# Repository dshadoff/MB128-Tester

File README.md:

# MB128-Tester
This project contains both a PC board to control (Backup, Restore, Test) PC Engine
Memory Base 128 devices, as well as the control software for that PC board.

The original PC board is based on an 'Adafruit Feather M0 Adalogger' microcontroller board, which
directly interfaces to PC Engine Memory Base 128 devices.

There is also an updated version which is based on the Seeed Studios Wio Terminal device, which is
more of a finished all-in-one unit with a screen.

This repository holds the software which runs on those devices, as well as the boards' design files.

The sketch was built within the Arduino IDE, but I found that the digitalWrite() and digitalRead()
functions were too slow: ~1uS per call, when I needed 3 to 4 times that speed.

Moreover, they could only manipulate one pin at a time, when I generally needed to write 2, or read 4.

As a result, you will see direct port reads/writes to the Cortex M0 (or M4) ports... see the comments at the
top of the sketch if this is confusing.

(Note: Older versions of this sketch were written for an older version of the board, which didn't have
status LEDs or pushbutton switches, and automatically started to read the MB128 at boot-up time.)

Instructions on use:
--------------------

To use any of the functionality, ensure that the MB128 is plugged into the port, and an SDCard is
inserted into the SDCard slot of the Microcontroller board.  Finally, then attach the USB cable
in order to apply power ot the board.

- M0 Adalogger board:
A short self-test will take place, and all of the LEDs will flash briefly.  Once this has completed
and the Feather's green LED is on, you may press a button.

- Wio Terminal:
A short self-test will take place, with status updates appearing on screen.  Once this has completed,
the screen will display a choice of operations (associated with the buttons across the top edge).

Backup:
-------
The device will backup the contents of the MB128 onto the SDCard, creating a file in the root
directory, with the filename: 'MB128_xx.SAV' (where 'xx' is a 2-digit number).  Multiple versions
of backups will be added to the SDCard until 99 versions have been reached.
A backup takes slightly over 10 seconds.

Restore:
--------
The device will use the highest-numbered 'MB128_xx.SAV' file in the root directory of the card,
and load the contents into the MB128.
A restore takes slightly over 10 seconds.

Test:
-----
The device will first create a temporary backup of the contents of the device, then will write,
read, and verify test patterns to all location on the MB128, finally restoring the original
contents.  The backup is saved into a file named 'TESTTEMP.BKP' in the root directory of the
SDCard.
A test takes slightly over one minute.

Error conditions:
-----------------
- If the 'SDCard Error' LED lights up at startup, there is a problem with the SDCard
- If the 'MB128 Error' LED lights up at startup, there is a problem with the MB128
(On the Wio Terminal version, clear error messages will appear on the screen).

- If either of the above LEDs go into a flashing state, this is an error which happened during
the process of reading or writing.  Please reset the device and/or turn the power off and back on

- In order to reset the device, there is a small pushbutton on the  microcontroller board. Do
not push this under normal circumstances, but you can press it if there is a flashing LED on
the MB128 reader.  If pressed, the MB128 may be interrupted in the middle of a protocol, causing
errors immedaitely afterward.  If this happens, unplug the MB128 from the reader, wait several
seconds, and plug it back in.  Then reset the microcontroller once again.

Additional information:
-----------------------
- If the USB is connected to a PC, and a terminal program is opened (19200 baud) for the
pseudo-serial port, messages indicating progress or errors will be displayed.

Original Board (Adalogger M0)
-----------------------------

Wio Terminal (Rev. A, in use)
-----------------------------

Daughterboard
-------------

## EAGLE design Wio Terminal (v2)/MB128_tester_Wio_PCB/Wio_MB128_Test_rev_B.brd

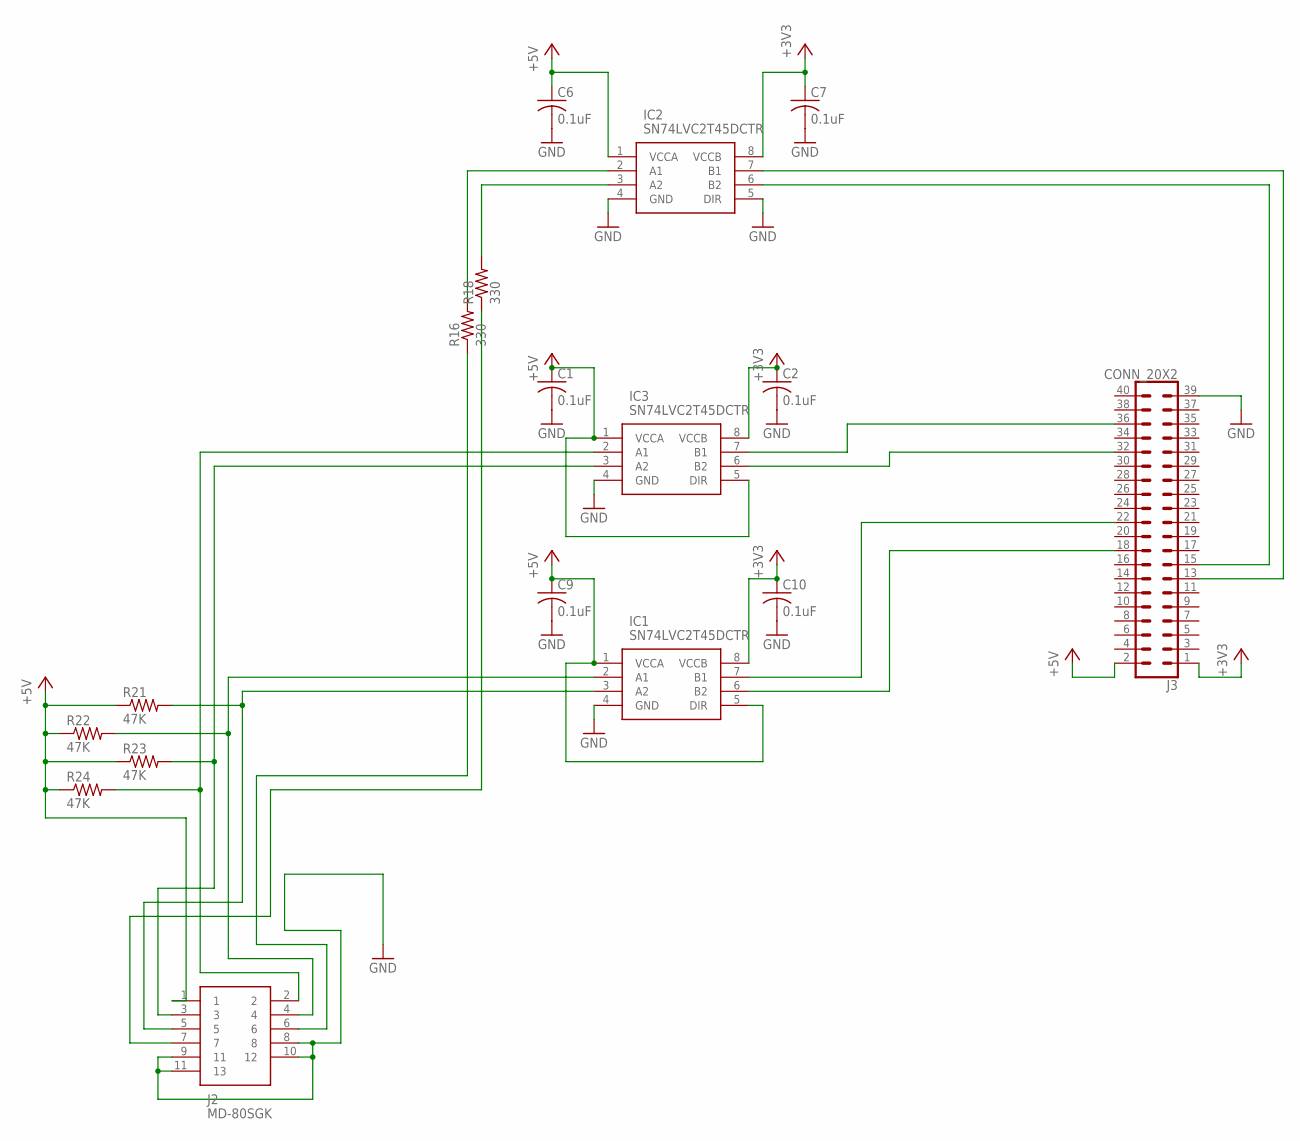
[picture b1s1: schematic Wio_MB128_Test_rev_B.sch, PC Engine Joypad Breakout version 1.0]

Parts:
C1, C2, C6, C7, C9, C10: 0.1uF; C0603
IC1, IC2, IC3: SN74LVC2T45DCTR; SOP65P400X130-8N
J2: MD-80SGK; MD80SGK
J3: CONN_20X2; 2X20
R16, R18: 330; R0603
R21, R22, R23, R24: 47K; R0603

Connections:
+3V3: C2.1, C7.1, C10.1, IC1.8 (VCCB), IC2.8 (VCCB), IC3.8 (VCCB), J3.1
+5V: C1.1, C6.1, C9.1, IC1.1 (VCCA), IC1.5 (DIR), IC2.1 (VCCA), IC3.1 (VCCA), IC3.5 (DIR), J2.1, J3.2, R21.1, R22.1, R23.1, R24.1
CLR: J2.7, R18.1
D11: IC1.7 (B1), J3.22
GND: C1.2, C2.2, C6.2, C7.2, C9.2, C10.2, IC1.4 (GND), IC2.4 (GND), IC2.5 (DIR), IC3.4 (GND), J2.8, J2.9 (11), J2.10 (12), J2.11 (13), J3.39
unnamed: IC2.7 (B1), J3.13
unnamed: IC3.3 (A2), J2.3, R23.2
unnamed: IC3.2 (A1), J2.2, R24.2
unnamed: IC2.6 (B2), J3.15
unnamed: IC1.6 (B2), J3.18
unnamed: IC2.2 (A1), R16.2
unnamed: IC1.2 (A1), J2.4, R22.2
unnamed: IC1.3 (A2), J2.5, R21.2
unnamed: IC2.3 (A2), R18.2
unnamed: IC3.7 (B1), J3.36
unnamed: IC3.6 (B2), J3.32
SEL: J2.6, R16.1

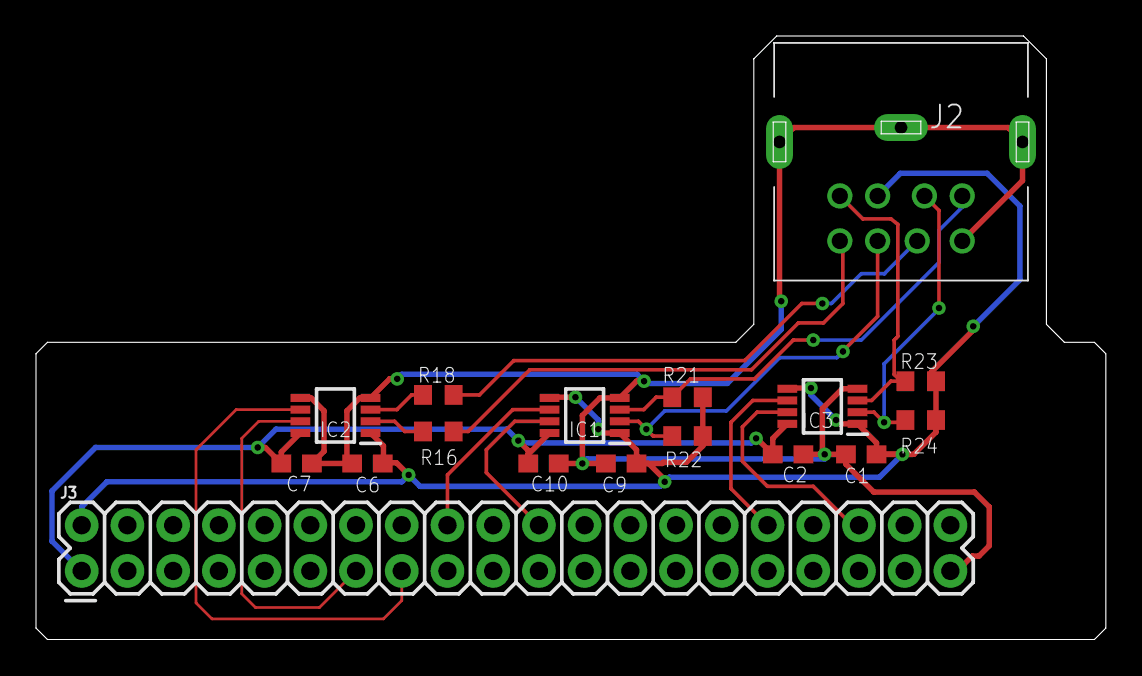
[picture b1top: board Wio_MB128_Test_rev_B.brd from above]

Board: 2 copper layers, 59.4 x 33.5 mm, 17 parts (0 on the bottom side), 17 nets.

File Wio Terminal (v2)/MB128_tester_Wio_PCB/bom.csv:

Qty,Designator,Footprint,Comment,LCSC Part # (optional),Description (optional)
6,"C1, C2, C6, C7, C9, C10",C0603,0.1uF 50V,C14663,Yageo CC0603KRX7R9BB104  100NF 50V 0603
2,"R16, R18",R0603,330 ohm 1%,C23138,Uniroyal Elec  0603WAF3300T5E 0603
4,"R21, R22, R23, R24",R0603,47K 1%,C25819,Uniroyal Elec  0603WAF4702T5E 0603
1,J3,2X20,Do not mount,Do not mount,Multi connection point. Often used as Generic Header-pin footprint for 0.1 inch spaced/style header connections
1,J2,MD80SGK,Do not mount,Do not mount,"Circular DIN Connectors mini-DIN, 8P jack, rt, through hole, full shield"
3,"IC1, IC2, IC3",SM-8_2.8x3.0x0.65P,SN74LVC2T45DCTR,C22672,"2-Bit Bus Transceiver, Translation SSOP8 SN74LVC2T45DCTR, Voltage Level Translator, Bus Transceiver LVC, 3-State 1.65"

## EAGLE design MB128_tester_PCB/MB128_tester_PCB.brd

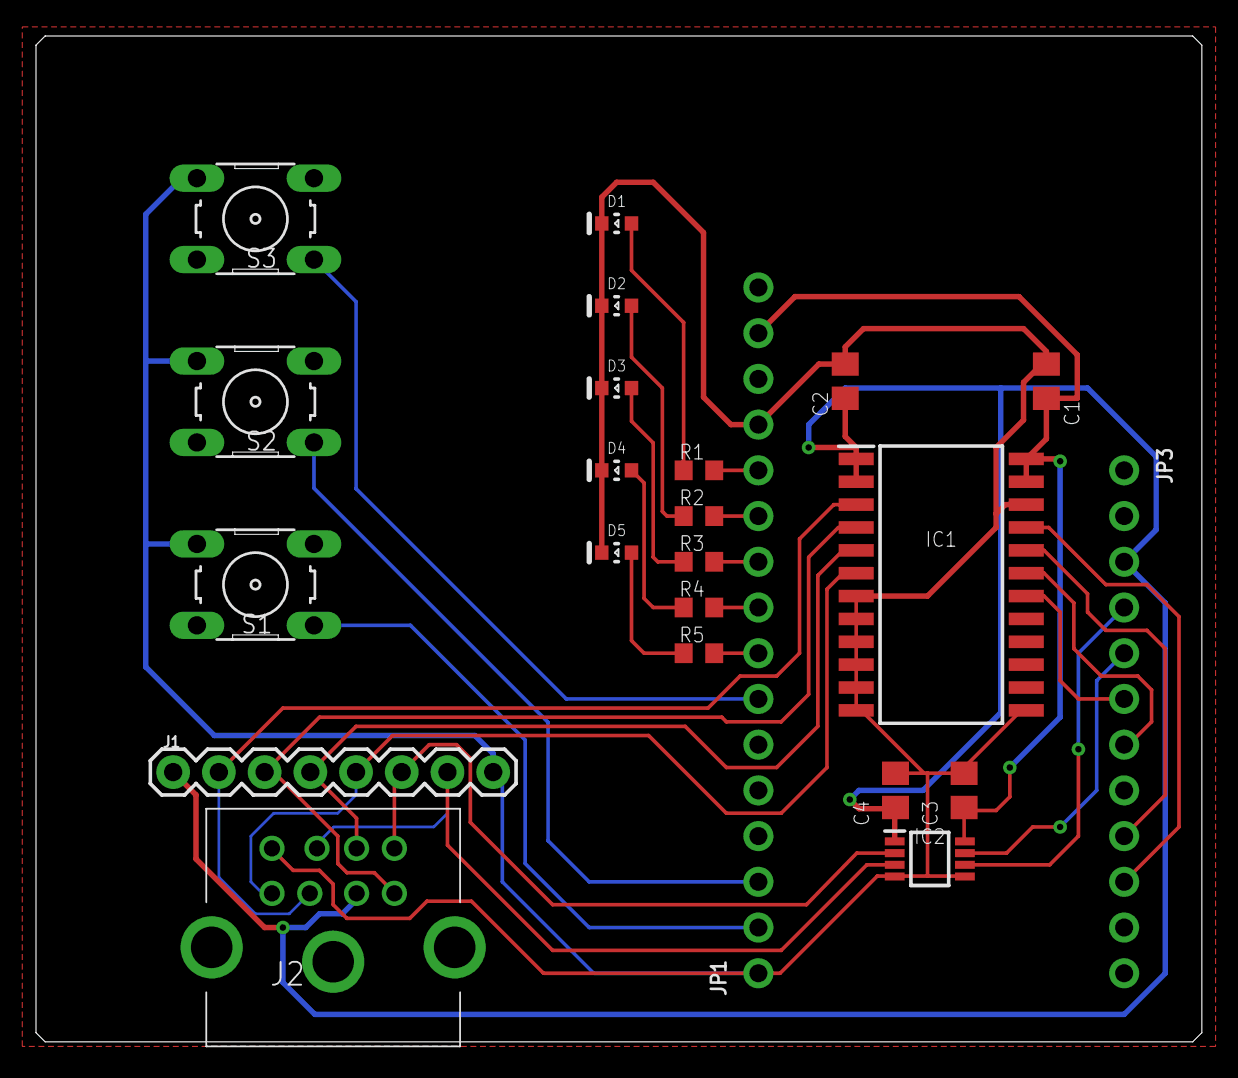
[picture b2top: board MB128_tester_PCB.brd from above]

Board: 2 copper layers, 64.8 x 55.9 mm, 23 parts (0 on the bottom side), 28 nets.

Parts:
C1, C2, C3, C4: 0.1uF; C0805
D1, D2: RED; WL-SMCC_0603_R/Y/V
D3: GREEN; WL-SMCC_0603_R/Y/V
D4: YELLOW; WL-SMCC_0603_R/Y/V
D5: BLUE; WL-SMCC_0603_R/Y/V
IC1: 74LVC4245AD,118; SOIC127P1032X265-24N
IC2: SN74LVC2T45DCTR; SOP65P400X130-8N
J1: Joypad; 1X08
J2: MD-80SGK; MD80SGK
JP1: 1X16_ROUND
JP3: 1X12_ROUND
R1, R2, R3, R4, R5: 1K; R0603
S1: TEST; B3F-10XX
S2: RESTORE; B3F-10XX
S3: BACKUP; B3F-10XX

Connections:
+3V3: C1.1, C3.1, IC1.23, IC1.24, IC2.8, JP1.15
+5V: C2.1, C4.1, IC1.1, IC1.2, IC2.1, J1.1, J2.1, JP3.3
A0: JP1.12, R1.2
A1: JP1.11, R2.2
A2: JP1.10, R3.2
A3: JP1.9, R4.2
A4: JP1.8, R5.2
A5: JP1.7, S3.1
D0: JP1.3, S2.1
D1: JP1.2, S1.1
D5: IC1.21, JP3.10
D6: IC1.20, JP3.9
D10: IC1.19, JP3.7
D11: IC1.18, JP3.6
D12: IC2.7, JP3.5
D13: IC2.6, JP3.4
GND: C1.2, C2.2, C3.2, C4.2, D1.1, D2.1, D3.1, D4.1, D5.1, IC1.7, IC1.8, IC1.9, IC1.10, IC1.11, IC1.12, IC1.13, IC1.22, IC2.4, IC2.5, J1.8, J2.8, JP1.1, JP1.13, S1.4, S2.4, S3.4
unnamed: D1.2, R1.1
unnamed: IC1.4, J1.3, J2.3
unnamed: IC1.3, J1.2, J2.2
unnamed: IC1.5, J1.4, J2.4
unnamed: IC1.6, J1.5, J2.5
unnamed: IC2.2, J1.6, J2.6
unnamed: IC2.3, J1.7, J2.7
unnamed: D2.2, R2.1
unnamed: D3.2, R3.1
unnamed: D4.2, R4.1
unnamed: D5.2, R5.1

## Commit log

2019-08-26 Initial commit This is the version prior to adding pushbuttons and LEDs to the circuit board
2019-09-01 Rough-in support for new board - switches and LEDs Also add TODOs for follow-up items
2019-09-17 Fairly substantial revision to clean up code and use pushbuttons
2019-10-28 Added functionality to 'Test' pushbutton, and minor adjustments to other functionality. Refactored the way reads/writes are structured.
2019-10-28 Update instructions
2019-10-29 Add PC Board design (Eagle) & gerbers
2019-10-29 Fix sketch name to match overall project
2019-11-18 Add support for KOEI Save-kun by removing a status bit check
2019-12-02 Update to ignore second status bit on write; also, verify written data to match what was written.
2021-01-15 Update version
    - Change the hierarchy to include both old and new versions
    - Add Wio version with screen I/O
    - Add Wio daughterboard
2021-01-28 Update board revision for Wio Terminal
    - Update board revision for Wio Terminal, including the files required for JLCPCB to perform SMD assembly of the board.
2021-01-28 Add pictures to readme

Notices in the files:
MB128_tester_PCB/MB128_tester_PCB.brd:
(C) 2019 David Shadoff
Wio Terminal (v2)/MB128_tester_Wio_PCB/Wio_MB128_Test_rev_B.brd:
(C)2021 David Shadoff
parts and their libraries:
SparkFun-Connectors: Licensing: Creative Commons ShareAlike 4.0 International - https://creativecommons.org/licenses/by-sa/4.0
microbuilder: This work is placed in the public domain, and may be freely used for commercial and non-commercial work with the following conditions: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
